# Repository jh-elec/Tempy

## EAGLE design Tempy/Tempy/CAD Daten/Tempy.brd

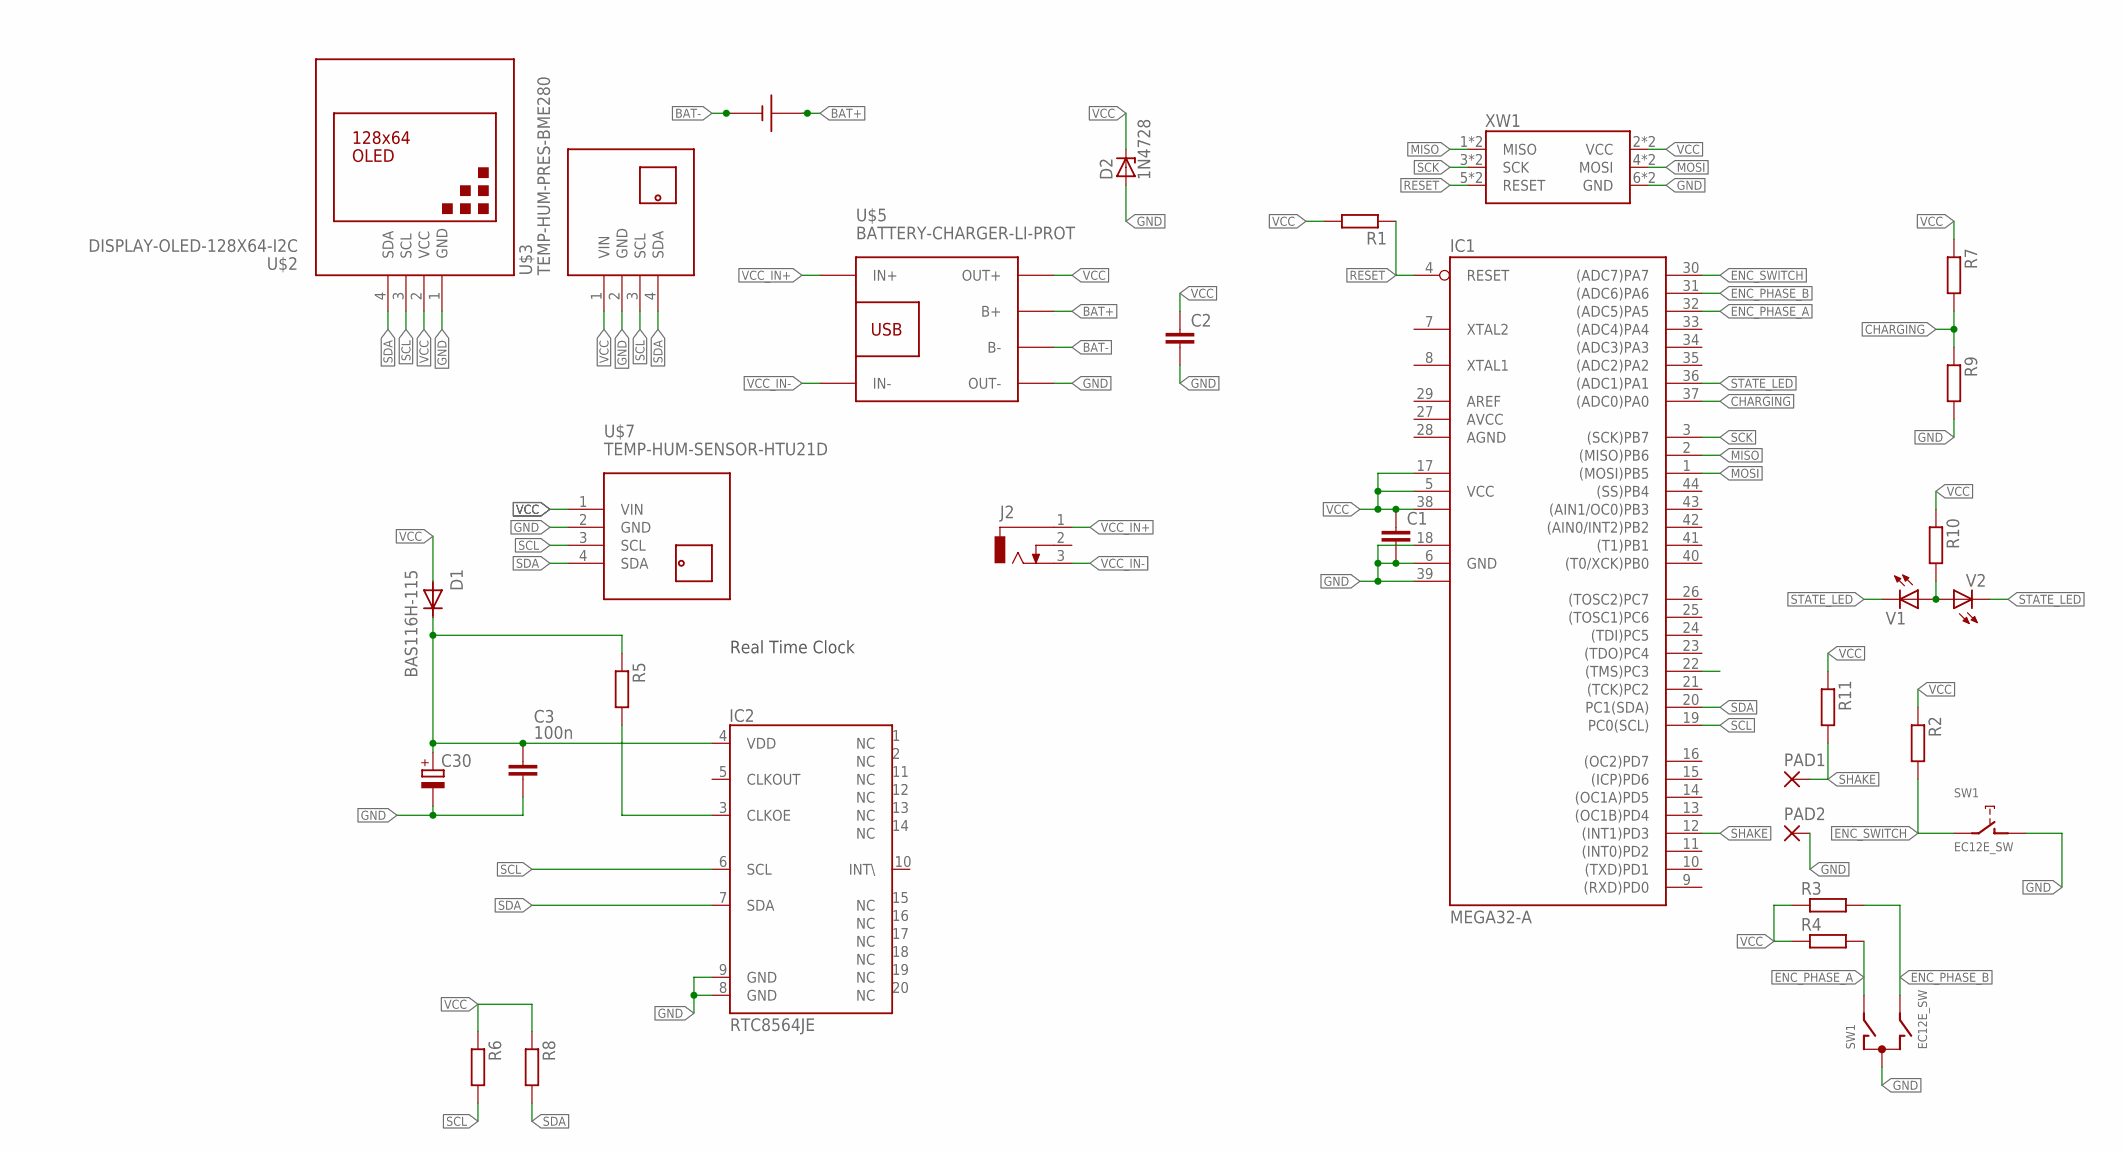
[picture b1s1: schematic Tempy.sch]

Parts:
C1, C2: C-EUC0805K; C0805K
C3: 100n; C0805
C30: PANASONIC-EN&SD-SERIESTHT_1; PANASONIC_SD_SERIES_STEHEND
D1: BAS116H-115; SOD123
D2: 1N4728; DO41Z10
IC1: MEGA32-A; TQFP44
IC2: RTC8564JESMD; VSOJ20
J2: DCJ0303
PAD1, PAD2: 2,15/1,0
R1, R2, R3, R4, R5, R6, R7, R8, R9, R10, R11: R-EU_R1206; R1206
SW1: EC12E_SW; ALPS_EC12E_SW
U$2: DISPLAY-OLED-128X64-I2C
U$3: TEMP-HUM-PRES-BME280
U$5: BATTERY-CHARGER-LI-PROT
U$7: TEMP-HUM-SENSOR-HTU21D
U$8: 18650PTH; 18650-CASE-PTH
V1: 0805SMD; 0805
V2: 1206SMD; 1206
XW1: WSL; WSL_KOMBI

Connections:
AGND: IC1.28 (AGND)
AREF: IC1.29 (AREF)
AVCC: IC1.27 (AVCC)
BAT+: U$5.B+, U$8.POS
BAT-: U$5.B-, U$8.NEG
CHARGING: IC1.37 ((ADC0)PA0), R7.2, R9.1
ENC_PHASE_A: IC1.32 ((ADC5)PA5), R4.2, SW1.A
ENC_PHASE_B: IC1.31 ((ADC6)PA6), R3.2, SW1.B
ENC_SWITCH: IC1.30 ((ADC7)PA7), R2.2, SW1.E (2)
GND: C1.2, C2.2, C3.2, C30.-, D2.A, IC1.6 (GND), IC1.18 (GND1), IC1.39 (GND2), IC2.8 (GND), IC2.9 (GND), PAD2.1, R9.2, SW1.C, SW1.D (1), U$2.1 (GND), U$3.2 (GND), U$5.OUT-, U$7.2 (GND), XW1.6 (GND), XW1.6.1 (GND)
MISO: IC1.2 ((MISO)PB6), XW1.1 (MISO), XW1.1.1 (MISO)
MOSI: IC1.1 ((MOSI)PB5), XW1.4 (MOSI), XW1.4.1 (MOSI)
unnamed: R10.2, V1.A, V2.A
unnamed: IC2.3 (CLKOE), R5.2
RESET: IC1.4 (RESET), R1.1, XW1.5 (RESET), XW1.5.1 (RESET)
SCK: IC1.3 ((SCK)PB7), XW1.3 (SCK), XW1.3.1 (SCK)
SCL: IC1.19 (PC0(SCL)), IC2.6 (SCL), R6.2, U$2.3 (SCL), U$3.3 (SCL), U$7.3 (SCL)
SDA: IC1.20 (PC1(SDA)), IC2.7 (SDA), R8.2, U$2.4 (SDA), U$3.4 (SDA), U$7.4 (SDA)
SHAKE: IC1.12 ((INT1)PD3), PAD1.1, R11.2
STATE_LED: IC1.36 ((ADC1)PA1), V1.K, V2.K
SUPPLY_RTC: C3.1, C30.+, D1.C, IC2.4 (VDD), R5.1
VCC: C1.1, C2.1, D1.A, D2.C, IC1.5 (VCC), IC1.17 (VCC1), IC1.38 (VCC2), R1.2, R2.1, R3.1, R4.1, R6.1, R7.1, R8.1, R10.1, R11.1, U$2.2 (VCC), U$3.1 (VIN), U$5.OUT+, U$7.1 (VIN), XW1.2 (VCC), XW1.2.1 (VCC)
VCC_IN+: J2.1, U$5.IN+
VCC_IN-: J2.3, U$5.IN-

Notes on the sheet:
Real Time Clock

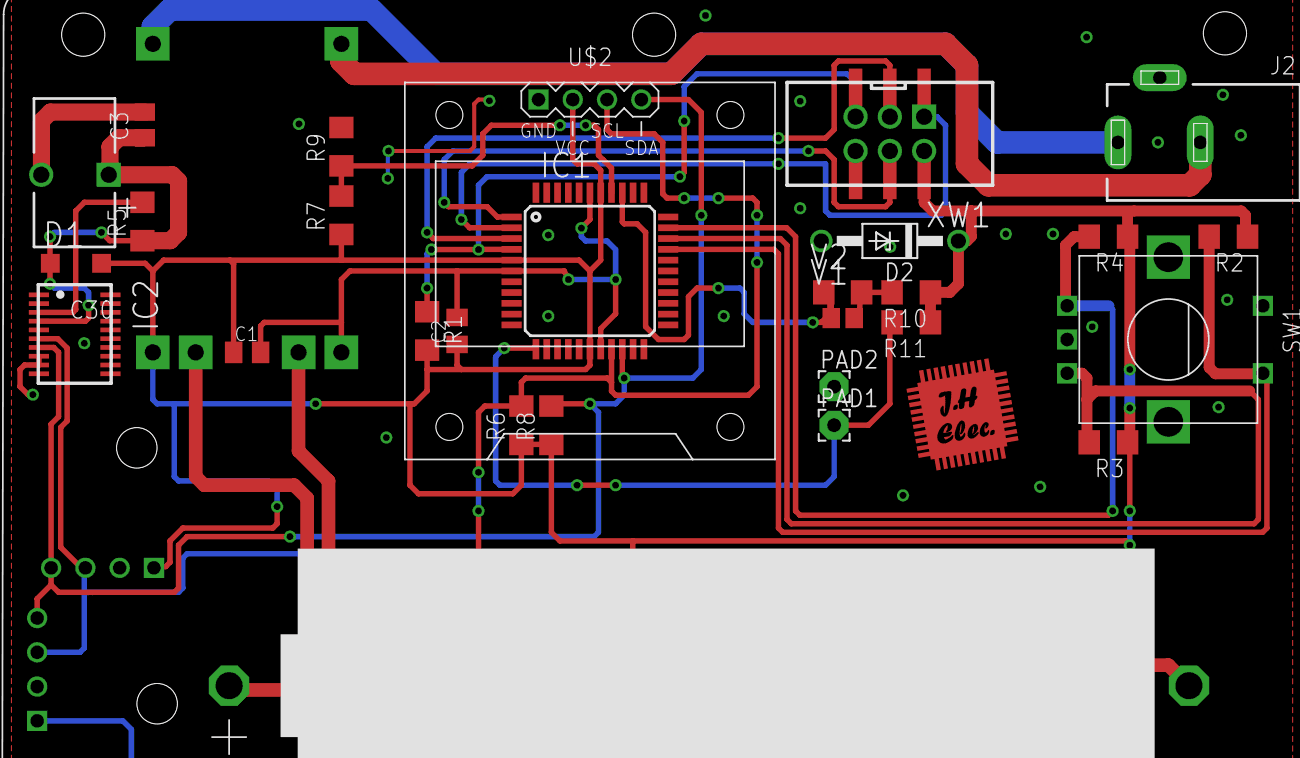
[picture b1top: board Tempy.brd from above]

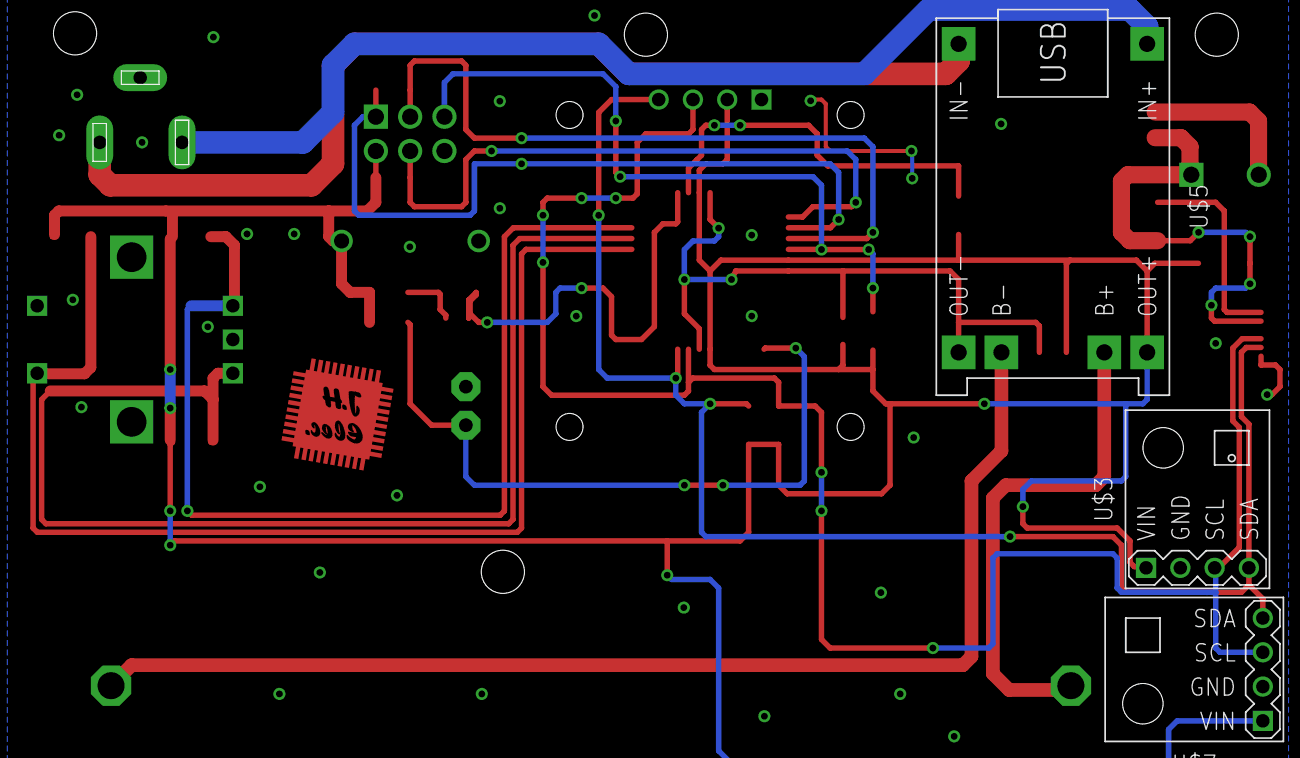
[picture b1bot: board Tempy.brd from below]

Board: 2 copper layers, 34 parts (3 on the bottom side), 21 nets.

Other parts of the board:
U$4: DONAU_KGB10
U$6: 25X25_BEST
U$9: 25X25

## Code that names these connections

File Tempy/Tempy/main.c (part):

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
#define DDRx(PORTx)				( * ( &PORTx - 1 ) )

#define STATE_LED_PORT			PORTA
#define STATE_LED_bp			PA1

#define STATE_LED_ON			STATE_LED_PORT &= ~(1<<STATE_LED_bp);
#define STATE_LED_OFF			STATE_LED_PORT |=  (1<<STATE_LED_bp);
#define STATE_LED_TOGGLE		STATE_LED_PORT ^=  (1<<STATE_LED_bp);

#define ENC_PORT				PORTA
#define ENC_PIN					PINA
#define ENC_PHASE_A_bp			PA5
#define ENC_PHASE_B_bp			PA6
#define ENC_SWITCH_bp			PA7

#define MEASUREMENT_AVERAGE		5

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
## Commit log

2018-07-23 Projekt veröffentlicht

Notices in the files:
parts and their libraries:
diy-modules: Released under the Creative Commons Attribution 4.0 International License: http://creativecommons.org/licenses/by/4.0
